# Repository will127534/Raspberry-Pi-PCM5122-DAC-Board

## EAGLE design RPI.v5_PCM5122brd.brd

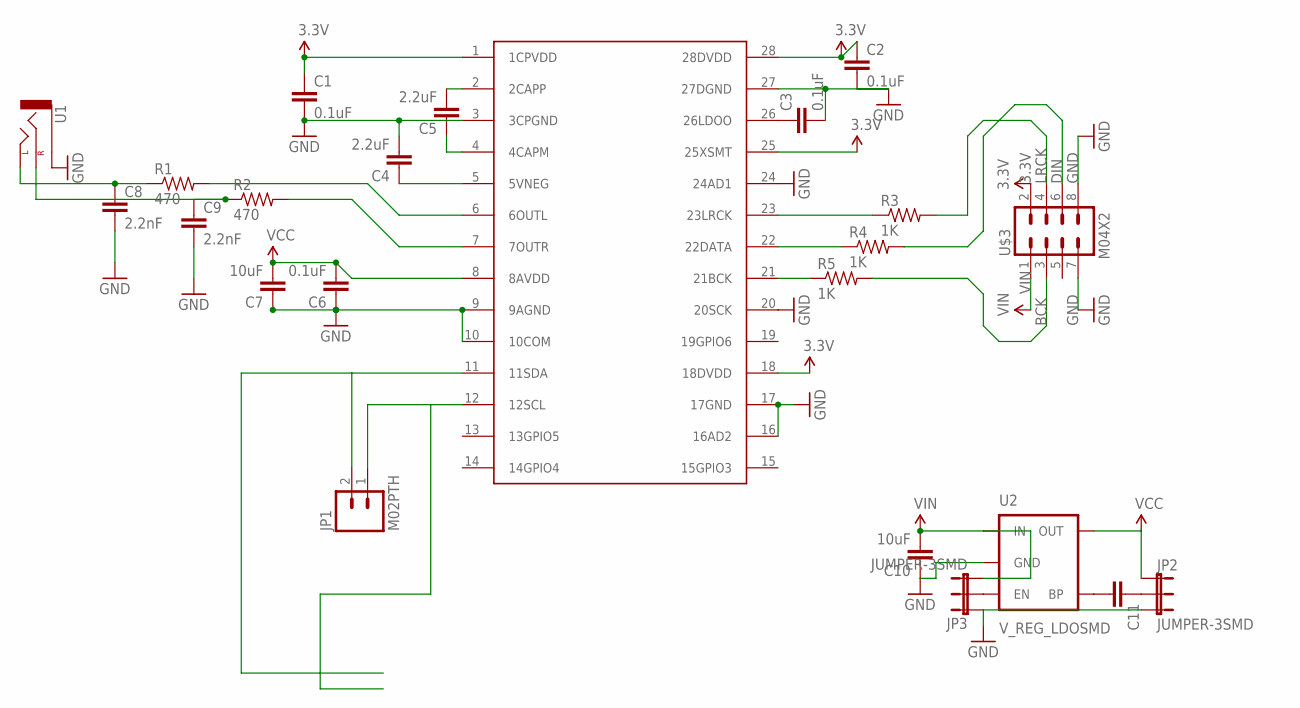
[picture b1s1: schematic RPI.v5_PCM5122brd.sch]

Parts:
C1, C2, C3, C6: 0.1uF; 0805
C4, C5: 2.2uF; 0805
C7, C10: 10uF; 0805
C8, C9: 2.2nF; CAP-PTH-5MM
C11: CAP0805; 0805
JP1: M02PTH; 1X02
JP2, JP3: JUMPER-3SMD; SJ_3
R1, R2: 470; AXIAL-0.4
R3, R4, R5: 1K; 0805
U1: AUDIO-JACKPTH; AUDIO-JACK
U2: V_REG_LDOSMD; SOT23-5
U$3: M04X2; 2X4
U$5: PCM5122; TSSOP28

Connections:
3.3V: C1.1, C2.1, U$3.2, U$5.1 (1CPVDD), U$5.18 (18DVDD), U$5.25 (25XSMT), U$5.28 (28DVDD)
BCK: R5.2, U$3.3
DIN: R4.2, U$3.6
GND: C1.2, C2.2, C3.2, C4.2, C6.1, C7.1, C8.2, C9.2, C10.1, JP2.3, JP3.1, U1.SLEEVE, U2.2 (GND), U$3.7, U$3.8, U$5.3 (3CPGND), U$5.9 (9AGND), U$5.10 (10COM), U$5.16 (16AD2), U$5.17 (17GND), U$5.20 (20SCK), U$5.24 (24AD1), U$5.27 (27DGND)
LRCK: R3.2, U$3.4
unnamed: C3.1, U$5.26 (26LDOO)
unnamed: C5.2, U$5.2 (2CAPP)
unnamed: C5.1, U$5.4 (4CAPM)
unnamed: C4.1, U$5.5 (5VNEG)
unnamed: C9.1, R2.P$1 (1), U1.RING (RIGHT)
unnamed: C8.1, R1.P$1 (1), U1.TIP (LEFT)
unnamed: R1.P$2 (2), U$5.6 (6OUTL)
unnamed: R2.P$2 (2), U$5.7 (7OUTR)
unnamed: R3.1, U$5.23 (23LRCK)
unnamed: R4.1, U$5.22 (22DATA)
unnamed: R5.1, U$5.21 (21BCK)
unnamed: JP1.2, U$5.11 (11SDA)
unnamed: JP1.1, U$5.12 (12SCL)
unnamed: C11.2, U2.4 (BP)
unnamed: C11.1, JP2.2
unnamed: JP3.2, U2.3 (EN)
VCC: C6.2, C7.2, JP2.1, U2.5 (OUT), U$5.8 (8AVDD)
VIN: C10.2, JP3.3, U2.1 (IN), U$3.1

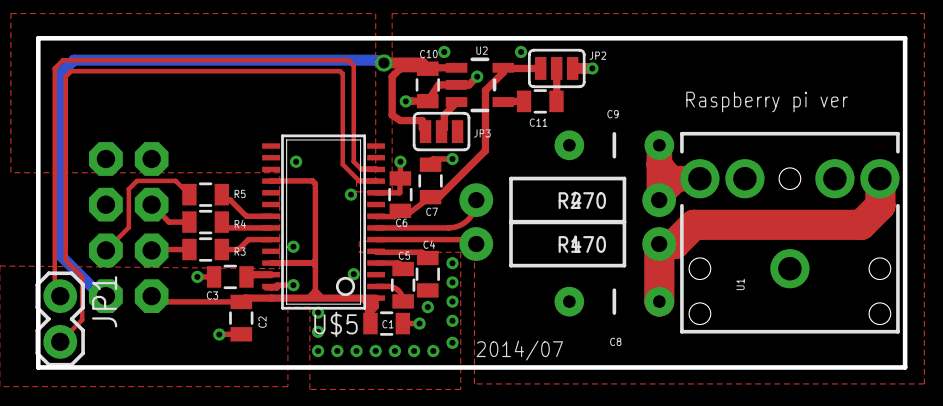
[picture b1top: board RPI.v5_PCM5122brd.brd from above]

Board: 2 copper layers, 48.2 x 18.3 mm, 23 parts (1 on the bottom side), 23 nets.

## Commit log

2015-07-15 :octocat: Added .gitattributes & .gitignore files
2015-07-15 Ver1.0
    PCB Layout Files

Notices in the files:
parts and their libraries:
SparkFun-Connectors: Licensing: CC v3.0 Share-Alike You are welcome to use this library for commercial purposes.
